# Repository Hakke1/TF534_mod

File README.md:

# TF534_mod
Slightly modified version of the TerribleFire TF534 V2c

- cleaned up silkscreen markings
- added through-holes for standard oscillator / socket
- added external activity LED breakout (5V)

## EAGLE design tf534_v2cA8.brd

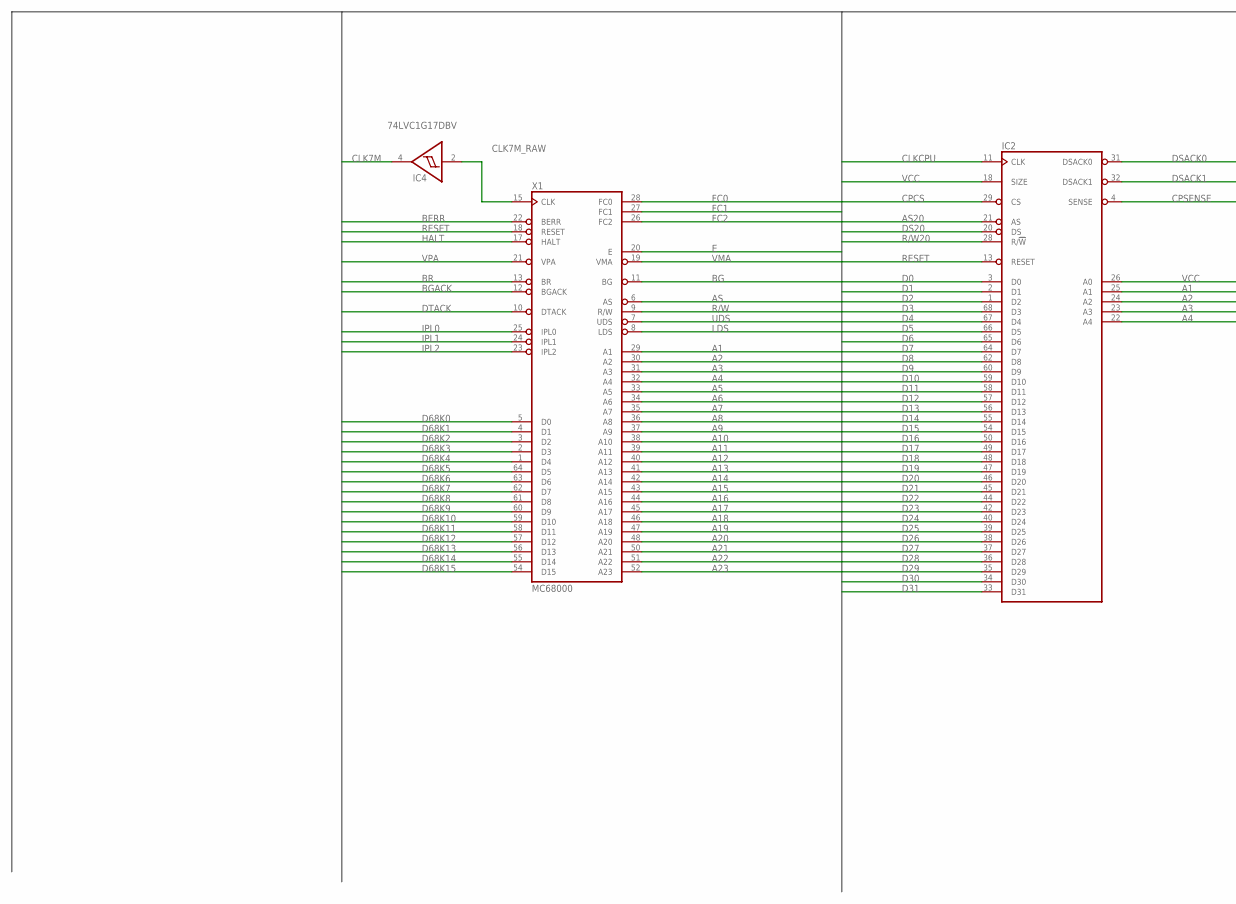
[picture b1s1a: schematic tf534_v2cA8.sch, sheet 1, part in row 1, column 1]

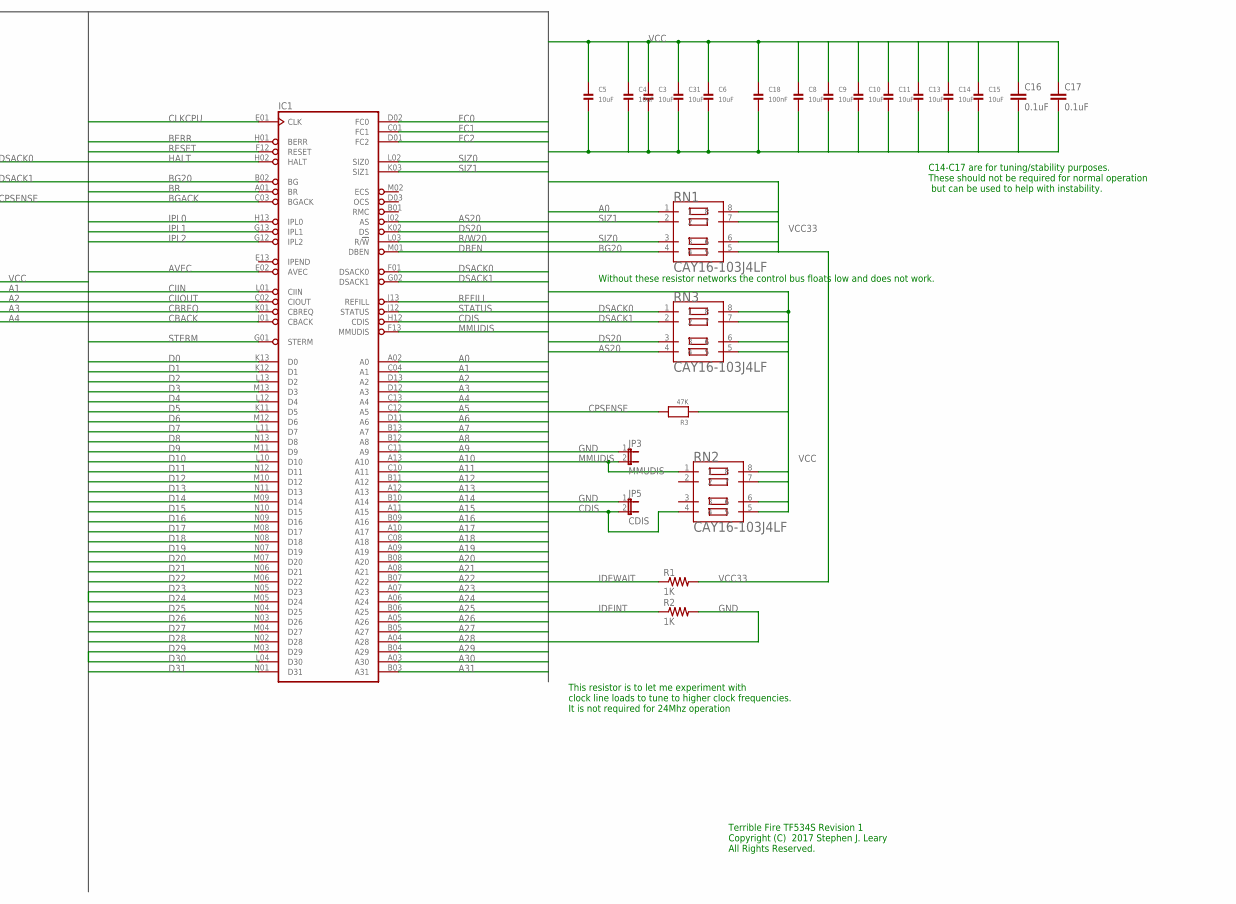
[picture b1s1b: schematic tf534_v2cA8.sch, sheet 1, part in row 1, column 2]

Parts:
C3, C4, C5, C6, C8, C9, C10, C11, C13, C14, C15, C31: 10uF; 1206
C16, C17: 0.1uF; 0603-CAP
C18: 100nF; 1206
IC1: MC68030RC; MPGA128
IC2: MC68881FN-SOC; PLCC68-S
IC4: 74LVC1G17DBV; SOT23-5
JP3: MMUDIS; 1X02
JP5: CDIS; 1X02
R1, R2: 1K; 0603
R3: 47K; 1206
RN1, RN2, RN3: CAY16-103J4LF; RESCAXE80P320X160-8N
X1: MC68000; DIL64

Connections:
A0: IC1.A02 (A0), RN1.1; also elsewhere on the board
A1: IC1.C04 (A1), IC2.25 (A1), X1.29 (A1); also elsewhere on the board
A2: IC1.D13 (A2), IC2.24 (A2), X1.30 (A2); also elsewhere on the board
A3: IC1.D12 (A3), IC2.23 (A3), X1.31 (A3); also elsewhere on the board
A4: IC1.C13 (A4), IC2.22 (A4), X1.32 (A4); also elsewhere on the board
A5: IC1.C12 (A5), X1.33 (A5); also elsewhere on the board
A6: IC1.D11 (A6), X1.34 (A6); also elsewhere on the board
A7: IC1.B13 (A7), X1.35 (A7); also elsewhere on the board
A8: IC1.B12 (A8), X1.36 (A8); also elsewhere on the board
A9: IC1.C11 (A9), X1.37 (A9); also elsewhere on the board
A10: IC1.A13 (A10), X1.38 (A10); also elsewhere on the board
A11: IC1.C10 (A11), X1.39 (A11); also elsewhere on the board
A12: IC1.B11 (A12), X1.40 (A12); also elsewhere on the board
A13: IC1.A12 (A13), X1.41 (A13); also elsewhere on the board
A14: IC1.B10 (A14), X1.42 (A14); also elsewhere on the board
A15: IC1.A11 (A15), X1.43 (A15); also elsewhere on the board
A16: IC1.B09 (A16), X1.44 (A16); also elsewhere on the board
A17: IC1.A10 (A17), X1.45 (A17); also elsewhere on the board
A18: IC1.C08 (A18), X1.46 (A18); also elsewhere on the board
A19: IC1.A09 (A19), X1.47 (A19); also elsewhere on the board
A20: IC1.B08 (A20), X1.48 (A20); also elsewhere on the board
A21: IC1.A08 (A21), X1.50 (A21); also elsewhere on the board
A22: IC1.B07 (A22), X1.51 (A22); also elsewhere on the board
A23: IC1.A07 (A23), X1.52 (A23); also elsewhere on the board
A24: IC1.A06 (A24); also elsewhere on the board
A25: IC1.B06 (A25); also elsewhere on the board
A26: IC1.A05 (A26); also elsewhere on the board
A27: IC1.B05 (A27); also elsewhere on the board
A28: IC1.A04 (A28); also elsewhere on the board
A29: IC1.B04 (A29); also elsewhere on the board
A30: IC1.A03 (A30); also elsewhere on the board
A31: IC1.B03 (A31); also elsewhere on the board
AS: X1.6 (AS); also elsewhere on the board
AS20: IC1.J02 (AS), IC2.21 (AS), RN3.4; also elsewhere on the board
AVEC: IC1.E02 (AVEC); also elsewhere on the board
BERR: IC1.H01 (BERR), X1.22 (BERR); also elsewhere on the board
BG: X1.11 (BG); also elsewhere on the board
BG20: IC1.B02 (BG), RN1.4; also elsewhere on the board
BGACK: IC1.C03 (BGACK), X1.12 (BGACK); also elsewhere on the board
BR: IC1.A01 (BR), X1.13 (BR)
CBACK: IC1.J01 (CBACK); also elsewhere on the board
CBREQ: IC1.K01 (CBREQ); also elsewhere on the board
CDIS: IC1.H12 (CDIS), JP5.2, RN2.4
CIIN: IC1.L01 (CIIN); also elsewhere on the board
CIIOUT: IC1.C02 (CIOUT)
CLK7M: IC4.4 (O); also elsewhere on the board
CLK7M_RAW: IC4.2 (I), X1.15 (CLK); also elsewhere on the board
CLKCPU: IC1.E01 (CLK), IC2.11 (CLK); also elsewhere on the board
CPCS: IC2.29 (CS); also elsewhere on the board
CPSENSE: IC2.4 (SENSE), R3.2; also elsewhere on the board
D0: IC1.K13 (D0), IC2.3 (D0); also elsewhere on the board
D1: IC1.K12 (D1), IC2.2 (D1); also elsewhere on the board
D2: IC1.L13 (D2), IC2.1 (D2); also elsewhere on the board
D3: IC1.M13 (D3), IC2.68 (D3); also elsewhere on the board
D4: IC1.L12 (D4), IC2.67 (D4); also elsewhere on the board
D5: IC1.K11 (D5), IC2.66 (D5); also elsewhere on the board
D6: IC1.M12 (D6), IC2.65 (D6); also elsewhere on the board
D7: IC1.L11 (D7), IC2.64 (D7); also elsewhere on the board
D8: IC1.N13 (D8), IC2.62 (D8); also elsewhere on the board
D9: IC1.M11 (D9), IC2.60 (D9); also elsewhere on the board
D10: IC1.L10 (D10), IC2.59 (D10); also elsewhere on the board
D11: IC1.N12 (D11), IC2.58 (D11); also elsewhere on the board
D12: IC1.M10 (D12), IC2.57 (D12); also elsewhere on the board
D13: IC1.N11 (D13), IC2.56 (D13); also elsewhere on the board
D14: IC1.M09 (D14), IC2.55 (D14); also elsewhere on the board
D15: IC1.N10 (D15), IC2.54 (D15); also elsewhere on the board
D16: IC1.N09 (D16), IC2.50 (D16); also elsewhere on the board
D17: IC1.M08 (D17), IC2.49 (D17); also elsewhere on the board
D18: IC1.N08 (D18), IC2.48 (D18); also elsewhere on the board
D19: IC1.N07 (D19), IC2.47 (D19); also elsewhere on the board
D20: IC1.M07 (D20), IC2.46 (D20); also elsewhere on the board
D21: IC1.N06 (D21), IC2.45 (D21); also elsewhere on the board
D22: IC1.M06 (D22), IC2.44 (D22); also elsewhere on the board
D23: IC1.N05 (D23), IC2.42 (D23); also elsewhere on the board
D24: IC1.M05 (D24), IC2.40 (D24); also elsewhere on the board
D25: IC1.N04 (D25), IC2.39 (D25); also elsewhere on the board
D26: IC1.N03 (D26), IC2.38 (D26); also elsewhere on the board
D27: IC1.M04 (D27), IC2.37 (D27); also elsewhere on the board
D28: IC1.N02 (D28), IC2.36 (D28); also elsewhere on the board
D29: IC1.M03 (D29), IC2.35 (D29); also elsewhere on the board
D30: IC1.L04 (D30), IC2.34 (D30); also elsewhere on the board
D31: IC1.N01 (D31), IC2.33 (D31); also elsewhere on the board
D68K0: X1.5 (D0); also elsewhere on the board
D68K1: X1.4 (D1); also elsewhere on the board
D68K2: X1.3 (D2); also elsewhere on the board
D68K3: X1.2 (D3); also elsewhere on the board
D68K4: X1.1 (D4); also elsewhere on the board
D68K5: X1.64 (D5); also elsewhere on the board
D68K6: X1.63 (D6); also elsewhere on the board
D68K7: X1.62 (D7); also elsewhere on the board
D68K8: X1.61 (D8); also elsewhere on the board
D68K9: X1.60 (D9); also elsewhere on the board
D68K10: X1.59 (D10); also elsewhere on the board
D68K11: X1.58 (D11); also elsewhere on the board
D68K12: X1.57 (D12); also elsewhere on the board
D68K13: X1.56 (D13); also elsewhere on the board
D68K14: X1.55 (D14); also elsewhere on the board
D68K15: X1.54 (D15); also elsewhere on the board
DBEN: IC1.M01 (DBEN)
DS20: IC1.K02 (DS), IC2.20 (DS), RN3.3; also elsewhere on the board
DSACK0: IC1.F01 (DSACK0), IC2.31 (DSACK0), RN3.1
DSACK1: IC1.G02 (DSACK1), IC2.32 (DSACK1), RN3.2; also elsewhere on the board
DTACK: X1.10 (DTACK); also elsewhere on the board
E: X1.20 (E); also elsewhere on the board
FC0: IC1.D02 (FC0), X1.28 (FC0); also elsewhere on the board
FC1: IC1.C01 (FC1), X1.27 (FC1); also elsewhere on the board
FC2: IC1.D01 (FC2), X1.26 (FC2); also elsewhere on the board
GND: C3.2, C4.2, C5.2, C6.2, C8.2, C9.2, C10.2, C11.2, C13.2, C14.2, C15.2, C16.2, C17.2, C18.2, C31.2, IC1.C05 (GND), IC1.C07 (GND), IC1.C09 (GND), IC1.E03 (GND), IC1.E11 (GND), IC1.F03 (GND), IC1.G03 (GND), IC1.G11 (GND), IC1.J03 (GND), IC1.J11 (GND), IC1.L05 (GND), IC1.L07 (GND), IC1.L08 (GND), IC1.L09 (GND), IC2.5 (GND), IC2.6 (GND), IC2.7 (GND), IC2.8 (GND), IC2.9 (GND), IC2.12 (GND), IC2.14 (GND), IC2.19 (GND), IC2.30 (GND), IC2.41 (GND), IC2.51 (GND), IC2.63 (GND), IC4.3 (GND), JP3.1, JP5.1, R2.2, X1.16 (GND), X1.53 (GND); also elsewhere on the board
HALT: IC1.H02 (HALT), X1.17 (HALT)
IDEINT: R2.1; also elsewhere on the board
IDEWAIT: R1.1; also elsewhere on the board
IPL0: IC1.H13 (IPL0), X1.25 (IPL0)
IPL1: IC1.G13 (IPL1), X1.24 (IPL1); also elsewhere on the board
IPL2: IC1.G12 (IPL2), X1.23 (IPL2); also elsewhere on the board
LDS: X1.8 (LDS); also elsewhere on the board
MMUDIS: IC1.F13 (MMUDIS), JP3.2, RN2.1
R/W: X1.9 (R/W); also elsewhere on the board
R/W20: IC1.L03 (R/!W), IC2.28 (R/!W); also elsewhere on the board
REFILL: IC1.J13 (REFILL)
RESET: IC1.F12 (RESET), IC2.13 (RESET), X1.18 (RESET); also elsewhere on the board
SIZ0: IC1.L02 (SIZ0), RN1.3; also elsewhere on the board
SIZ1: IC1.K03 (SIZ1), RN1.2; also elsewhere on the board
STATUS: IC1.J12 (STATUS)
STERM: IC1.G01 (STERM); also elsewhere on the board
UDS: X1.7 (UDS); also elsewhere on the board
VCC: C3.1, C4.1, C5.1, C6.1, C8.1, C9.1, C10.1, C11.1, C13.1, C14.1, C15.1, C16.1, C17.1, C18.1, C31.1, IC1.C06 (VCC), IC1.D04 (VCC), IC1.D10 (VCC), IC1.F02 (VCC), IC1.F11 (VCC), IC1.H03 (VCC), IC1.H11 (VCC), IC1.K04 (VCC), IC1.K10 (VCC), IC1.L06 (VCC), IC2.10 (VCC), IC2.16 (VCC), IC2.17 (VCC), IC2.18 (SIZE), IC2.26 (A0), IC2.27 (VCC), IC2.43 (VCC), IC2.52 (VCC), IC2.53 (VCC), IC2.61 (VCC), IC4.5 (VCC), R3.1, RN2.5, RN2.6, RN2.7, RN2.8, RN3.5, RN3.6, RN3.7, RN3.8, X1.14 (VCC), X1.49 (VCC); also elsewhere on the board
VCC33: R1.2, RN1.5, RN1.6, RN1.7, RN1.8; also elsewhere on the board
VMA: X1.19 (VMA); also elsewhere on the board
VPA: X1.21 (VPA); also elsewhere on the board

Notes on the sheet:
This resistor is to let me experiment with clock line loads to tune to higher clock frequencies. It is not required for 24Mhz operation
C14-C17 are for tuning/stability purposes. These should not be required for normal operation but can be used to help with instability.
Without these resistor networks the control bus floats low and does not work.
Terrible Fire TF534S Revision 1 Copyright (C) 2017 Stephen J. Leary All Rights Reserved.

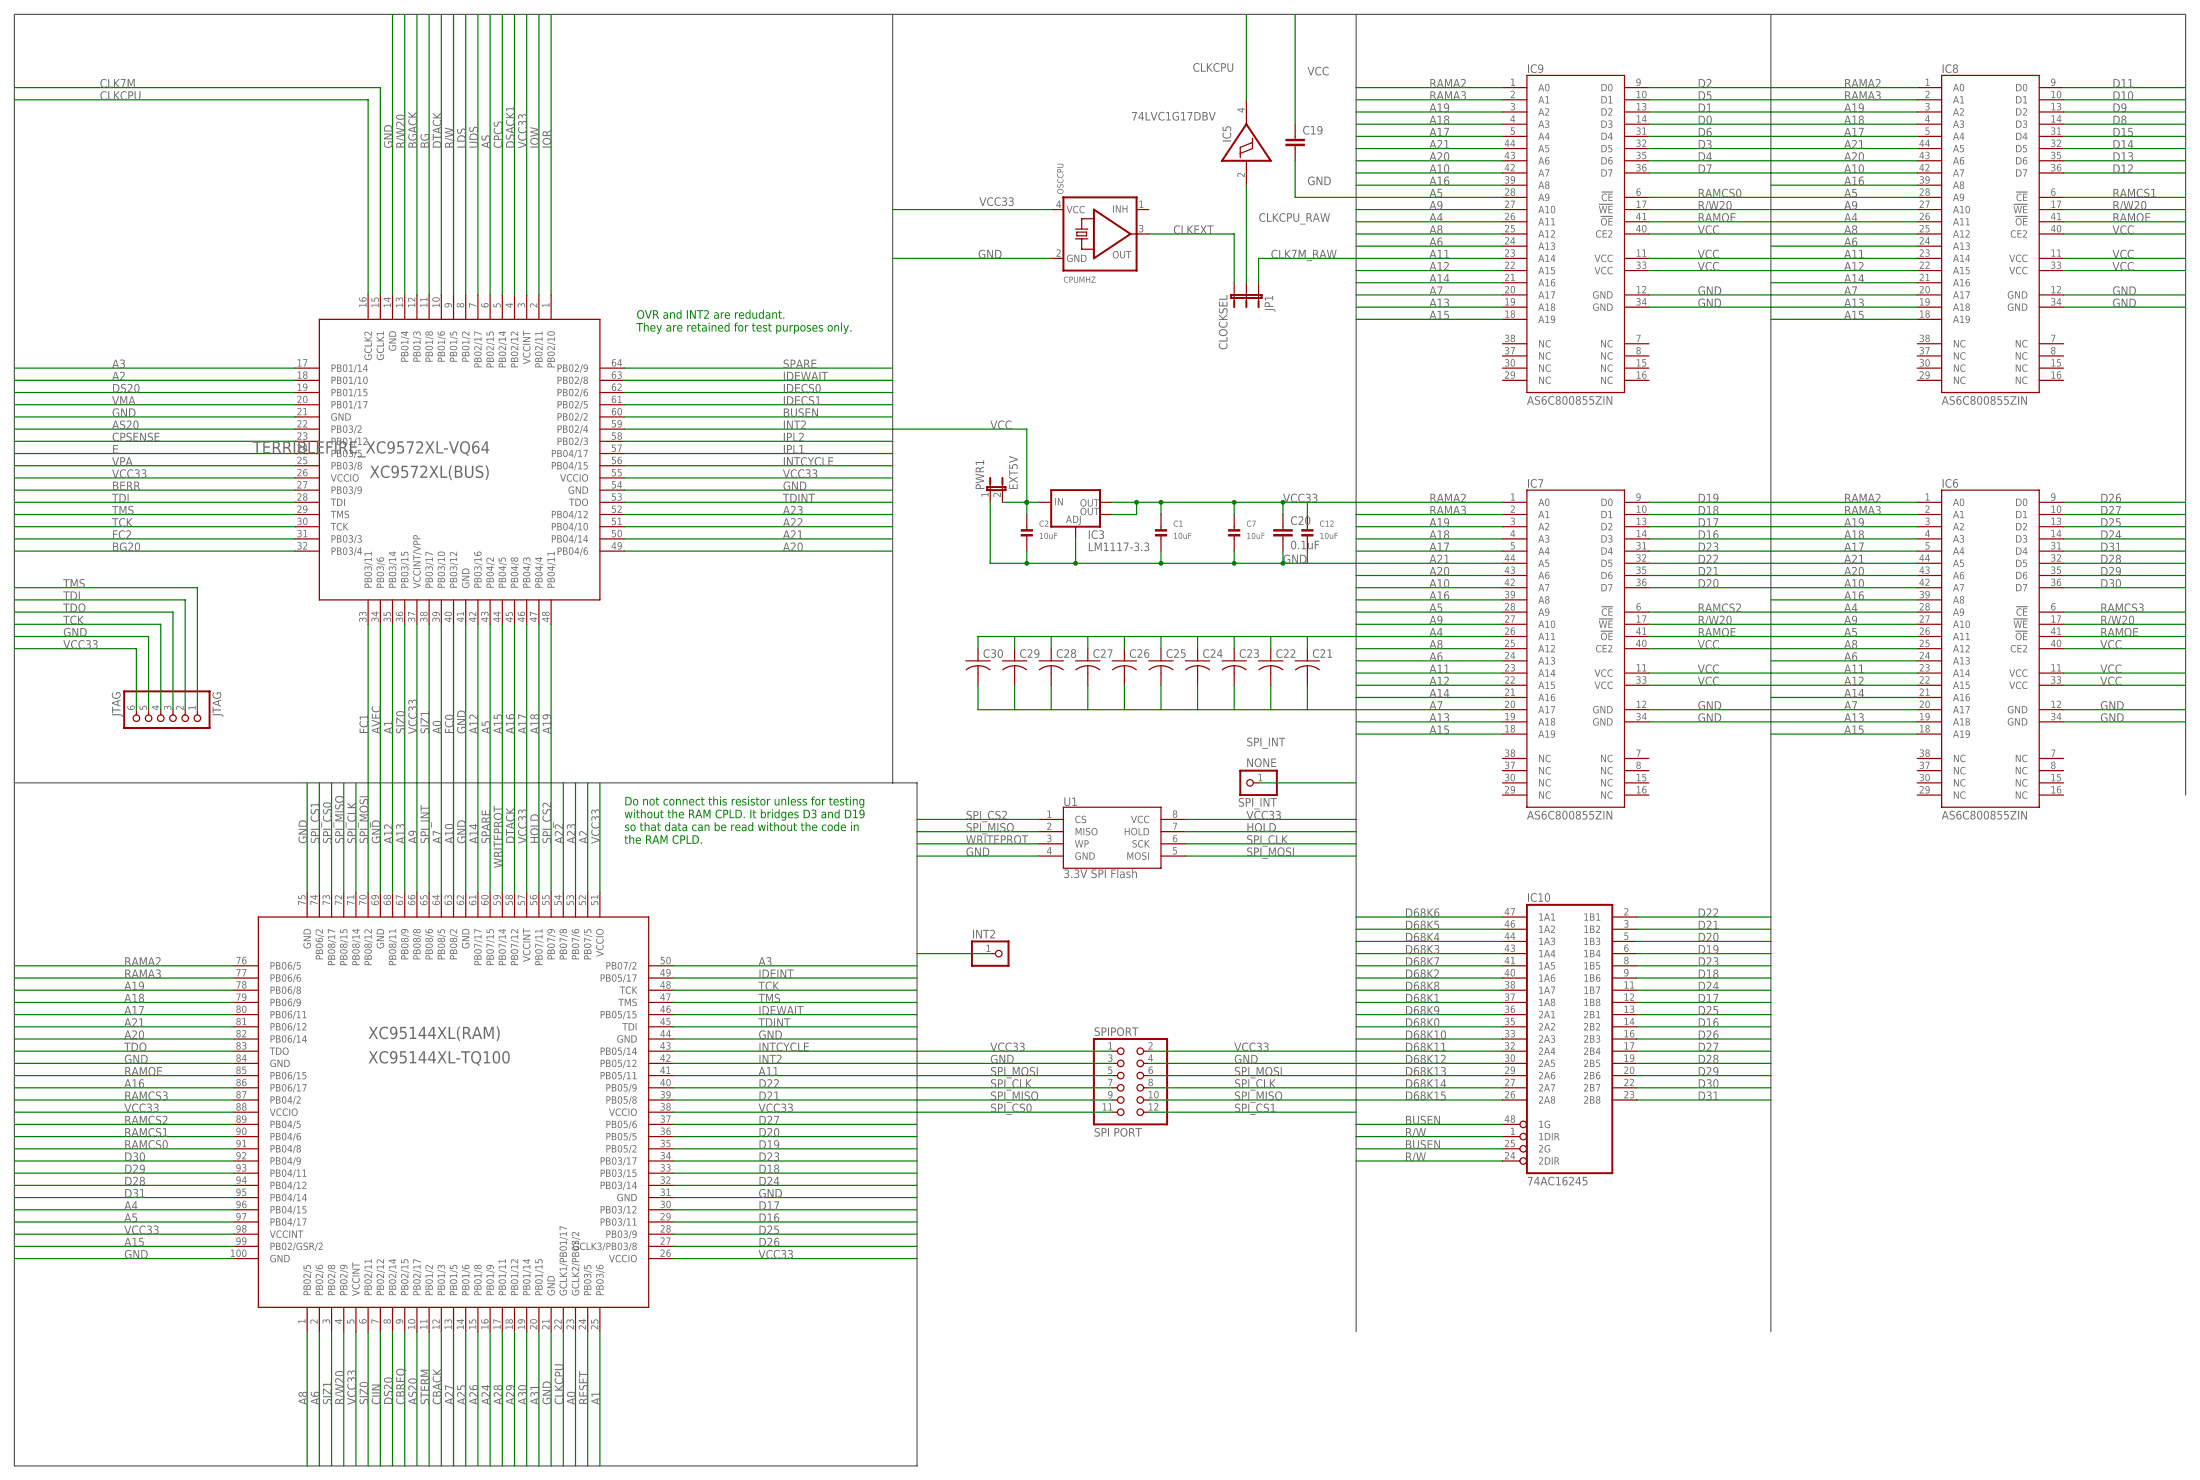
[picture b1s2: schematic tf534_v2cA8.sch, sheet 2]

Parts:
C1, C2, C7, C12: 10uF; 1206
C19: CC0603; C0603
C20: 0.1uF; 0603-CAP
C21, C22, C23, C24, C25, C26, C27, C28, C29, C30: C-USC0603; C0603
IC3: LM1117-3.3; SOT223
IC5: 74LVC1G17DBV; SOT23-5
IC6, IC7, IC8, IC9: AS6C800855ZIN; TSOP44-II
IC10: 74AC16245; SSOP48DL
INT2: PINHD-1X1; 1X01
JP1: CLOCKSEL; 1X03
JTAG: JTAG; 1X06_ROUND
OSCCPU: CPUMHZ; OSC_7X5MM
PWR1: EXT5V; 1X02
SPIPORT: SPI PORT; 2X06
SPI_INT: NONE; 1X01
U1: 3.3V SPI Flash; SO08
XC9572XL(BUS): TERRIBLEFIRE_XC9572XL-VQ64; TERRIBLEFIRE_VQ64
XC95144XL(RAM): XC95144XL-TQ100; TQFP100

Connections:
A0: XC9572XL(BUS).39 (PB03/10), XC95144XL(RAM).23 (GCLK2/PB03/2); also elsewhere on the board
A1: XC9572XL(BUS).35 (PB03/14), XC95144XL(RAM).25 (PB03/6); also elsewhere on the board
A2: XC9572XL(BUS).18 (PB01/10), XC95144XL(RAM).52 (PB07/5); also elsewhere on the board
A3: XC9572XL(BUS).17 (PB01/14), XC95144XL(RAM).50 (PB07/2); also elsewhere on the board
A4: IC6.28 (A9), IC7.26 (A11), IC8.26 (A11), IC9.26 (A11), XC95144XL(RAM).96 (PB04/15); also elsewhere on the board
A5: IC6.26 (A11), IC7.28 (A9), IC8.28 (A9), IC9.28 (A9), XC9572XL(BUS).43 (PB04/2), XC95144XL(RAM).97 (PB04/17); also elsewhere on the board
A6: IC6.24 (A13), IC7.24 (A13), IC8.24 (A13), IC9.24 (A13), XC95144XL(RAM).2 (PB02/6); also elsewhere on the board
A7: IC6.20 (A17), IC7.20 (A17), IC8.20 (A17), IC9.20 (A17), XC95144XL(RAM).64 (PB08/5); also elsewhere on the board
A8: IC6.25 (A12), IC7.25 (A12), IC8.25 (A12), IC9.25 (A12), XC95144XL(RAM).1 (PB02/5); also elsewhere on the board
A9: IC6.27 (A10), IC7.27 (A10), IC8.27 (A10), IC9.27 (A10), XC95144XL(RAM).66 (PB08/8); also elsewhere on the board
A10: IC6.42 (A7), IC7.42 (A7), IC8.42 (A7), IC9.42 (A7), XC95144XL(RAM).63 (PB08/2); also elsewhere on the board
A11: IC6.23 (A14), IC7.23 (A14), IC8.23 (A14), IC9.23 (A14), XC95144XL(RAM).41 (PB05/11); also elsewhere on the board
A12: IC6.22 (A15), IC7.22 (A15), IC8.22 (A15), IC9.22 (A15), XC9572XL(BUS).42 (PB03/16), XC95144XL(RAM).68 (PB08/11); also elsewhere on the board
A13: IC6.19 (A18), IC7.19 (A18), IC8.19 (A18), IC9.19 (A18), XC95144XL(RAM).67 (PB08/9); also elsewhere on the board
A14: IC6.21 (A16), IC7.21 (A16), IC8.21 (A16), IC9.21 (A16), XC95144XL(RAM).61 (PB07/17); also elsewhere on the board
A15: IC6.18 (A19), IC7.18 (A19), IC8.18 (A19), IC9.18 (A19), XC9572XL(BUS).44 (PB04/5), XC95144XL(RAM).99 (PB02/GSR/2); also elsewhere on the board
A16: IC6.39 (A8), IC7.39 (A8), IC8.39 (A8), IC9.39 (A8), XC9572XL(BUS).45 (PB04/8), XC95144XL(RAM).86 (PB06/17); also elsewhere on the board
A17: IC6.5 (A4), IC7.5 (A4), IC8.5 (A4), IC9.5 (A4), XC9572XL(BUS).46 (PB04/3), XC95144XL(RAM).80 (PB06/11); also elsewhere on the board
A18: IC6.4 (A3), IC7.4 (A3), IC8.4 (A3), IC9.4 (A3), XC9572XL(BUS).47 (PB04/4), XC95144XL(RAM).79 (PB06/9); also elsewhere on the board
A19: IC6.3 (A2), IC7.3 (A2), IC8.3 (A2), IC9.3 (A2), XC9572XL(BUS).48 (PB04/11), XC95144XL(RAM).78 (PB06/8); also elsewhere on the board
A20: IC6.43 (A6), IC7.43 (A6), IC8.43 (A6), IC9.43 (A6), XC9572XL(BUS).49 (PB04/6), XC95144XL(RAM).82 (PB06/14); also elsewhere on the board
A21: IC6.44 (A5), IC7.44 (A5), IC8.44 (A5), IC9.44 (A5), XC9572XL(BUS).50 (PB04/14), XC95144XL(RAM).81 (PB06/12); also elsewhere on the board
A22: XC9572XL(BUS).51 (PB04/10), XC95144XL(RAM).54 (PB07/8); also elsewhere on the board
A23: XC9572XL(BUS).52 (PB04/12), XC95144XL(RAM).53 (PB07/6); also elsewhere on the board
A24: XC95144XL(RAM).16 (PB01/9); also elsewhere on the board
A25: XC95144XL(RAM).14 (PB01/6); also elsewhere on the board
A26: XC95144XL(RAM).15 (PB01/8); also elsewhere on the board
A27: XC95144XL(RAM).13 (PB01/5); also elsewhere on the board
A28: XC95144XL(RAM).17 (PB01/11); also elsewhere on the board
A29: XC95144XL(RAM).18 (PB01/12); also elsewhere on the board
A30: XC95144XL(RAM).19 (PB01/14); also elsewhere on the board
A31: XC95144XL(RAM).20 (PB01/15); also elsewhere on the board
AS: XC9572XL(BUS).6 (PB02/15); also elsewhere on the board
AS20: XC9572XL(BUS).22 (PB03/2), XC95144XL(RAM).10 (PB02/17); also elsewhere on the board
AVEC: XC9572XL(BUS).34 (PB03/6); also elsewhere on the board
BERR: XC9572XL(BUS).27 (PB03/9); also elsewhere on the board
BG: XC9572XL(BUS).11 (PB01/8); also elsewhere on the board
BG20: XC9572XL(BUS).32 (PB03/4); also elsewhere on the board
BGACK: XC9572XL(BUS).12 (PB01/3); also elsewhere on the board
BUSEN: IC10.25 (2G), IC10.48 (1G), XC9572XL(BUS).60 (PB02/2)
CBACK: XC95144XL(RAM).12 (PB01/3); also elsewhere on the board
CBREQ: XC95144XL(RAM).9 (PB02/15); also elsewhere on the board
CIIN: XC95144XL(RAM).7 (PB02/12); also elsewhere on the board
CLK7M: XC9572XL(BUS).15 (GCLK1); also elsewhere on the board
CLK7M_RAW: JP1.1; also elsewhere on the board
CLKCPU: IC5.4 (O), XC9572XL(BUS).16 (GCLK2), XC95144XL(RAM).22 (GCLK1/PB01/17); also elsewhere on the board
CLKCPU_RAW: IC5.2 (I), JP1.2
CLKEXT: JP1.3, OSCCPU.3 (OUT)
CPCS: XC9572XL(BUS).5 (PB02/14); also elsewhere on the board
CPSENSE: XC9572XL(BUS).23 (PB01/12); also elsewhere on the board
D0: IC9.14 (D3); also elsewhere on the board
D1: IC9.13 (D2); also elsewhere on the board
D2: IC9.9 (D0); also elsewhere on the board
D3: IC9.32 (D5); also elsewhere on the board
D4: IC9.35 (D6); also elsewhere on the board
D5: IC9.10 (D1); also elsewhere on the board
D6: IC9.31 (D4); also elsewhere on the board
D7: IC9.36 (D7); also elsewhere on the board
D8: IC8.14 (D3); also elsewhere on the board
D9: IC8.13 (D2); also elsewhere on the board
D10: IC8.10 (D1); also elsewhere on the board
D11: IC8.9 (D0); also elsewhere on the board
D12: IC8.36 (D7); also elsewhere on the board
D13: IC8.35 (D6); also elsewhere on the board
D14: IC8.32 (D5); also elsewhere on the board
D15: IC8.31 (D4); also elsewhere on the board
D16: IC7.14 (D3), IC10.14 (2B2), XC95144XL(RAM).29 (PB03/11); also elsewhere on the board
D17: IC7.13 (D2), IC10.12 (1B8), XC95144XL(RAM).30 (PB03/12); also elsewhere on the board
D18: IC7.10 (D1), IC10.9 (1B6), XC95144XL(RAM).33 (PB03/15); also elsewhere on the board
D19: IC7.9 (D0), IC10.6 (1B4), XC95144XL(RAM).35 (PB05/2); also elsewhere on the board
D20: IC7.36 (D7), IC10.5 (1B3), XC95144XL(RAM).36 (PB05/5); also elsewhere on the board
D21: IC7.35 (D6), IC10.3 (1B2), XC95144XL(RAM).39 (PB05/8); also elsewhere on the board
D22: IC7.32 (D5), IC10.2 (1B1), XC95144XL(RAM).40 (PB05/9); also elsewhere on the board
D23: IC7.31 (D4), IC10.8 (1B5), XC95144XL(RAM).34 (PB03/17); also elsewhere on the board
D24: IC6.14 (D3), IC10.11 (1B7), XC95144XL(RAM).32 (PB03/14); also elsewhere on the board
D25: IC6.13 (D2), IC10.13 (2B1), XC95144XL(RAM).28 (PB03/9); also elsewhere on the board
D26: IC6.9 (D0), IC10.16 (2B3), XC95144XL(RAM).27 (GCLK3/PB03/8); also elsewhere on the board
D27: IC6.10 (D1), IC10.17 (2B4), XC95144XL(RAM).37 (PB05/6); also elsewhere on the board
D28: IC6.32 (D5), IC10.19 (2B5), XC95144XL(RAM).94 (PB04/12); also elsewhere on the board
D29: IC6.35 (D6), IC10.20 (2B6), XC95144XL(RAM).93 (PB04/11); also elsewhere on the board
D30: IC6.36 (D7), IC10.22 (2B7), XC95144XL(RAM).92 (PB04/9); also elsewhere on the board
D31: IC6.31 (D4), IC10.23 (2B8), XC95144XL(RAM).95 (PB04/14); also elsewhere on the board
D68K0: IC10.35 (2A2); also elsewhere on the board
D68K1: IC10.37 (1A8); also elsewhere on the board
D68K2: IC10.40 (1A6); also elsewhere on the board
D68K3: IC10.43 (1A4); also elsewhere on the board
D68K4: IC10.44 (1A3); also elsewhere on the board
D68K5: IC10.46 (1A2); also elsewhere on the board
D68K6: IC10.47 (1A1); also elsewhere on the board
D68K7: IC10.41 (1A5); also elsewhere on the board
D68K8: IC10.38 (1A7); also elsewhere on the board
D68K9: IC10.36 (2A1); also elsewhere on the board
D68K10: IC10.33 (2A3); also elsewhere on the board
D68K11: IC10.32 (2A4); also elsewhere on the board
D68K12: IC10.30 (2A5); also elsewhere on the board
D68K13: IC10.29 (2A6); also elsewhere on the board
D68K14: IC10.27 (2A7); also elsewhere on the board
D68K15: IC10.26 (2A8); also elsewhere on the board
DS20: XC9572XL(BUS).19 (PB01/15), XC95144XL(RAM).8 (PB02/14); also elsewhere on the board
DSACK1: XC9572XL(BUS).4 (PB02/12); also elsewhere on the board
DTACK: XC9572XL(BUS).10 (PB01/6), XC95144XL(RAM).58 (PB07/12); also elsewhere on the board
E: XC9572XL(BUS).24 (PB03/5); also elsewhere on the board
FC0: XC9572XL(BUS).40 (PB03/12); also elsewhere on the board
FC1: XC9572XL(BUS).33 (PB03/11); also elsewhere on the board
FC2: XC9572XL(BUS).31 (PB03/3); also elsewhere on the board
GND: C1.2, C2.2, C7.2, C12.2, C19.2, C20.2, C21.2, C22.2, C23.2, C24.2, C25.2, C26.2, C27.2, C28.2, C29.2, C30.2, IC3.1 (ADJ), IC5.3 (GND), IC6.12 (GND), IC6.34 (GND), IC7.12 (GND), IC7.34 (GND), IC8.12 (GND), IC8.34 (GND), IC9.12 (GND), IC9.34 (GND), IC10.4 (GND), IC10.10 (GND), IC10.15 (GND), IC10.21 (GND), IC10.28 (GND), IC10.34 (GND), IC10.39 (GND), IC10.45 (GND), JTAG.5, OSCCPU.2 (GND), PWR1.1, SPIPORT.3, SPIPORT.4, U1.4 (GND), XC9572XL(BUS).14 (GND), XC9572XL(BUS).21 (GND), XC9572XL(BUS).41 (GND), XC9572XL(BUS).54 (GND), XC95144XL(RAM).21 (GND), XC95144XL(RAM).31 (GND), XC95144XL(RAM).44 (GND), XC95144XL(RAM).62 (GND), XC95144XL(RAM).69 (GND), XC95144XL(RAM).75 (GND), XC95144XL(RAM).84 (GND), XC95144XL(RAM).100 (GND); also elsewhere on the board
HOLD: U1.7 (HOLD), XC95144XL(RAM).56 (PB07/11)
IDECS0: XC9572XL(BUS).62 (PB02/6); also elsewhere on the board
IDECS1: XC9572XL(BUS).61 (PB02/5); also elsewhere on the board
IDEINT: XC95144XL(RAM).49 (PB05/17); also elsewhere on the board
IDEWAIT: XC9572XL(BUS).63 (PB02/8), XC95144XL(RAM).46 (PB05/15); also elsewhere on the board
INT2: INT2.1, XC9572XL(BUS).59 (PB02/4), XC95144XL(RAM).42 (PB05/12)
INTCYCLE: XC9572XL(BUS).56 (PB04/15), XC95144XL(RAM).43 (PB05/14)
IOR: XC9572XL(BUS).1 (PB02/10); also elsewhere on the board
IOW: XC9572XL(BUS).2 (PB02/11); also elsewhere on the board
IPL1: XC9572XL(BUS).57 (PB04/17); also elsewhere on the board
IPL2: XC9572XL(BUS).58 (PB02/3); also elsewhere on the board
LDS: XC9572XL(BUS).8 (PB01/2); also elsewhere on the board
R/W: IC10.1 (1DIR), IC10.24 (2DIR), XC9572XL(BUS).9 (PB01/5); also elsewhere on the board
R/W20: IC6.17 (!WE), IC7.17 (!WE), IC8.17 (!WE), IC9.17 (!WE), XC9572XL(BUS).13 (PB01/4), XC95144XL(RAM).4 (PB02/9); also elsewhere on the board
RAMA2: IC6.1 (A0), IC7.1 (A0), IC8.1 (A0), IC9.1 (A0), XC95144XL(RAM).76 (PB06/5)
RAMA3: IC6.2 (A1), IC7.2 (A1), IC8.2 (A1), IC9.2 (A1), XC95144XL(RAM).77 (PB06/6)
RAMCS0: IC9.6 (!CE), XC95144XL(RAM).91 (PB04/8)
RAMCS1: IC8.6 (!CE), XC95144XL(RAM).90 (PB04/6)
RAMCS2: IC7.6 (!CE), XC95144XL(RAM).89 (PB04/5)
RAMCS3: IC6.6 (!CE), XC95144XL(RAM).87 (PB04/2)
RAMOE: IC6.41 (!OE), IC7.41 (!OE), IC8.41 (!OE), IC9.41 (!OE), XC95144XL(RAM).85 (PB06/15)
RESET: XC95144XL(RAM).24 (PB03/5); also elsewhere on the board
SIZ0: XC9572XL(BUS).36 (PB03/15), XC95144XL(RAM).6 (PB02/11); also elsewhere on the board
SIZ1: XC9572XL(BUS).38 (PB03/17), XC95144XL(RAM).3 (PB02/8); also elsewhere on the board
SPARE: XC9572XL(BUS).64 (PB02/9), XC95144XL(RAM).60 (PB07/15)
SPI_CLK: SPIPORT.7, SPIPORT.8, U1.6 (SCK), XC95144XL(RAM).71 (PB08/14)
SPI_CS0: SPIPORT.11, XC95144XL(RAM).73 (PB08/17)
SPI_CS1: SPIPORT.12, XC95144XL(RAM).74 (PB06/2)
SPI_CS2: U1.1 (CS), XC95144XL(RAM).55 (PB07/9)
SPI_INT: SPI_INT.1, XC95144XL(RAM).65 (PB08/6)
SPI_MISO: SPIPORT.9, SPIPORT.10, U1.2 (MISO), XC95144XL(RAM).72 (PB08/15)
SPI_MOSI: SPIPORT.5, SPIPORT.6, U1.5 (MOSI), XC95144XL(RAM).70 (PB08/12)
STERM: XC95144XL(RAM).11 (PB01/2); also elsewhere on the board
TCK: JTAG.4, XC9572XL(BUS).30 (TCK), XC95144XL(RAM).48 (TCK)
TDI: JTAG.2, XC9572XL(BUS).28 (TDI)
TDINT: XC9572XL(BUS).53 (TDO), XC95144XL(RAM).45 (TDI)
TDO: JTAG.3, XC95144XL(RAM).83 (TDO)
TMS: JTAG.1, XC9572XL(BUS).29 (TMS), XC95144XL(RAM).47 (TMS)
UDS: XC9572XL(BUS).7 (PB02/17); also elsewhere on the board
VCC: C2.1, C19.1, IC3.3 (IN), IC5.5 (VCC), IC6.11 (VCC), IC6.33 (VCC), IC6.40 (CE2), IC7.11 (VCC), IC7.33 (VCC), IC7.40 (CE2), IC8.11 (VCC), IC8.33 (VCC), IC8.40 (CE2), IC9.11 (VCC), IC9.33 (VCC), IC9.40 (CE2), IC10.7 (VCC), IC10.18 (VCC), IC10.31 (VCC), IC10.42 (VCC), PWR1.2; also elsewhere on the board
VCC33: C1.1, C7.1, C12.1, C20.1, C21.1, C22.1, C23.1, C24.1, C25.1, C26.1, C27.1, C28.1, C29.1, C30.1, IC3.2 (OUT), IC3.4 (OUT), JTAG.6, OSCCPU.4 (VCC), SPIPORT.1, SPIPORT.2, U1.8 (VCC), XC9572XL(BUS).3 (VCCINT), XC9572XL(BUS).26 (VCCIO), XC9572XL(BUS).37 (VCCINT/VPP), XC9572XL(BUS).55 (VCCIO), XC95144XL(RAM).5 (VCCINT), XC95144XL(RAM).26 (VCCIO), XC95144XL(RAM).38 (VCCIO), XC95144XL(RAM).51 (VCCIO), XC95144XL(RAM).57 (VCCINT), XC95144XL(RAM).88 (VCCIO), XC95144XL(RAM).98 (VCCINT); also elsewhere on the board
VMA: XC9572XL(BUS).20 (PB01/17); also elsewhere on the board
VPA: XC9572XL(BUS).25 (PB03/8); also elsewhere on the board
WRITEPROT: U1.3 (WP), XC95144XL(RAM).59 (PB07/14)

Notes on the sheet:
OVR and INT2 are redudant. They are retained for test purposes only.
Do not connect this resistor unless for testing without the RAM CPLD. It bridges D3 and D19 so that data can be read without the code in the RAM CPLD.

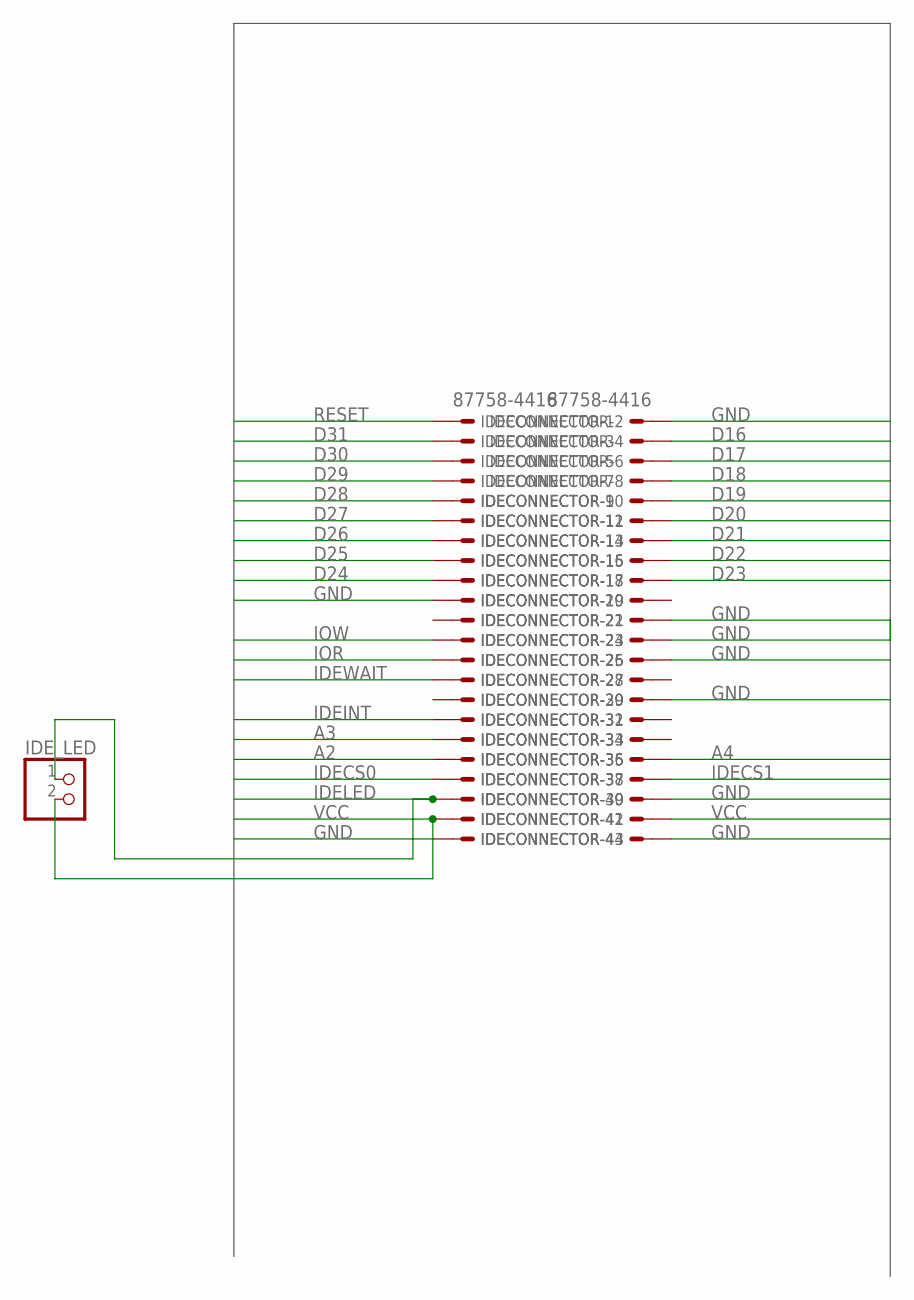
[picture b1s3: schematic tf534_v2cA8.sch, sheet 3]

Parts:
IDECONNECTOR: 87758-4416
IDE_LED: PINHD-1X2; 1X02

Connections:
A2: IDECONNECTOR.35; also elsewhere on the board
A3: IDECONNECTOR.33; also elsewhere on the board
A4: IDECONNECTOR.36; also elsewhere on the board
D16: IDECONNECTOR.4; also elsewhere on the board
D17: IDECONNECTOR.6; also elsewhere on the board
D18: IDECONNECTOR.8; also elsewhere on the board
D19: IDECONNECTOR.10; also elsewhere on the board
D20: IDECONNECTOR.12; also elsewhere on the board
D21: IDECONNECTOR.14; also elsewhere on the board
D22: IDECONNECTOR.16; also elsewhere on the board
D23: IDECONNECTOR.18; also elsewhere on the board
D24: IDECONNECTOR.17; also elsewhere on the board
D25: IDECONNECTOR.15; also elsewhere on the board
D26: IDECONNECTOR.13; also elsewhere on the board
D27: IDECONNECTOR.11; also elsewhere on the board
D28: IDECONNECTOR.9; also elsewhere on the board
D29: IDECONNECTOR.7; also elsewhere on the board
D30: IDECONNECTOR.5; also elsewhere on the board
D31: IDECONNECTOR.3; also elsewhere on the board
GND: IDECONNECTOR.2, IDECONNECTOR.19, IDECONNECTOR.22, IDECONNECTOR.24, IDECONNECTOR.26, IDECONNECTOR.30, IDECONNECTOR.40, IDECONNECTOR.43, IDECONNECTOR.44; also elsewhere on the board
IDECS0: IDECONNECTOR.37; also elsewhere on the board
IDECS1: IDECONNECTOR.38; also elsewhere on the board
IDEINT: IDECONNECTOR.31; also elsewhere on the board
IDELED: IDECONNECTOR.39, IDE_LED.1
IDEWAIT: IDECONNECTOR.27; also elsewhere on the board
IOR: IDECONNECTOR.25; also elsewhere on the board
IOW: IDECONNECTOR.23; also elsewhere on the board
RESET: IDECONNECTOR.1; also elsewhere on the board
VCC: IDECONNECTOR.41, IDECONNECTOR.42, IDE_LED.2; also elsewhere on the board

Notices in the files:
tf534_v2cA8.brd:
(C) 2018 S.J Leary
parts and their libraries:
microbuilder: This work is placed in the public domain, and may be freely used for commercial and non-commercial work with the following conditions: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
SparkFun-Retired: Licensing:Creative Commons ShareAlike 4.0 International - https://creativecommons.org/licenses/by-sa/4.0
